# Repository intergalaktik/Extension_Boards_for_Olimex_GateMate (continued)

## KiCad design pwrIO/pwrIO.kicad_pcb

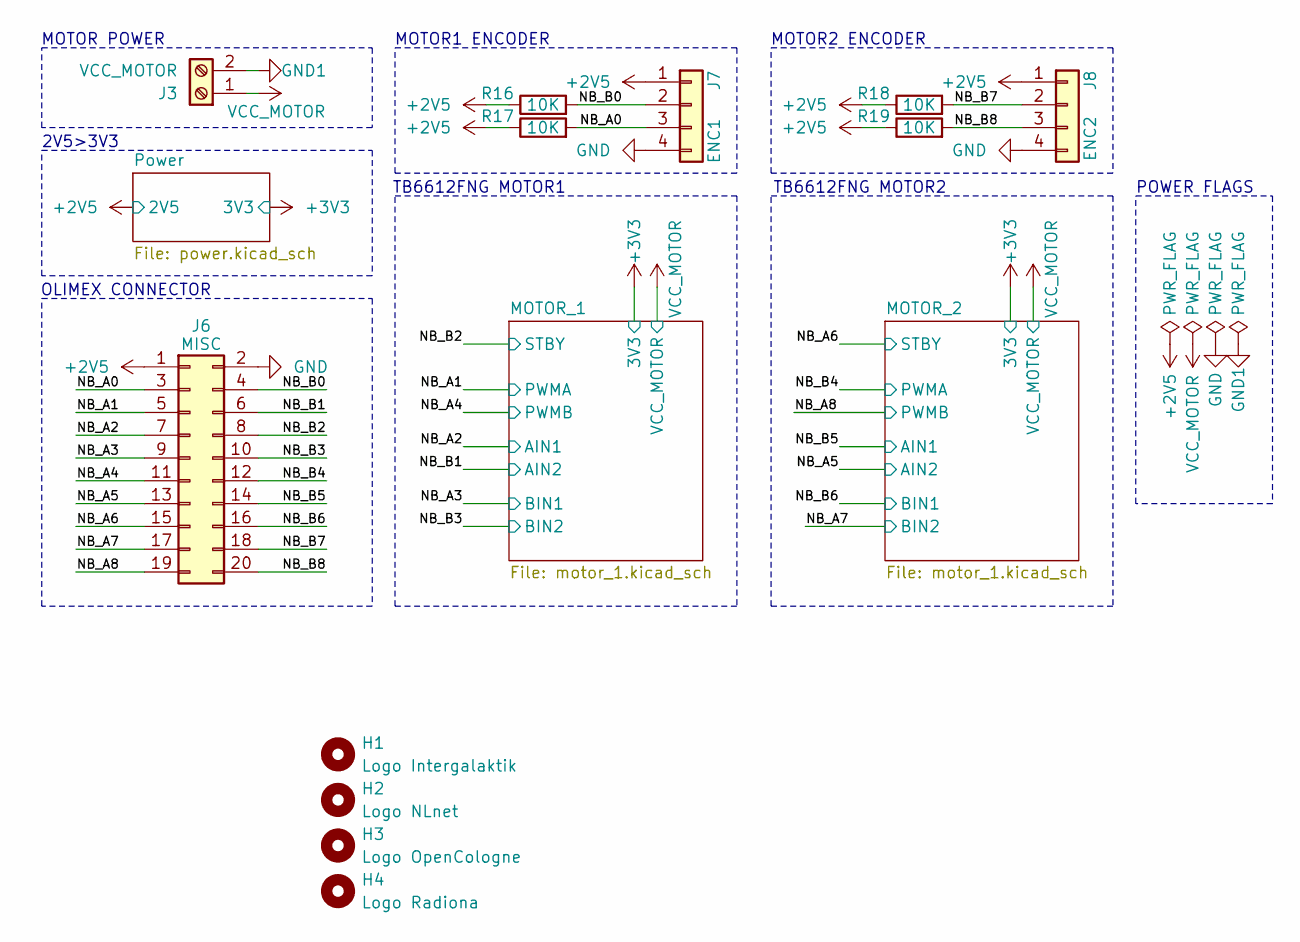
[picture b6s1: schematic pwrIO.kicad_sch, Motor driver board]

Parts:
H1: Logo Intergalaktik; intergalaktik
H2: Logo NLnet; nlnet
H3: Logo OpenCologne; open_cologne
H4: Logo Radiona; radiona
J3: VCC_MOTOR; TerminalBlock_Phoenix_MPT-0,5-2-2.54_1x02_P2.54mm_Horizontal
J6: MISC; PinSocket_2x10_P2.54mm_Vertical_SMD
J7: ENC1; PinSocket_1x04_P2.54mm_Vertical
J8: ENC2; PinSocket_1x04_P2.54mm_Vertical
R16, R17, R18, R19: 10K; R_0402_1005Metric

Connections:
+2V5: J6.1, J7.1, J8.1, R16.1, R17.1, R18.1, R19.1; also elsewhere on the board
/NB_A0: J6.3, J7.3, R17.2
/NB_A1: J6.5; also elsewhere on the board
/NB_A2: J6.7; also elsewhere on the board
/NB_A3: J6.9; also elsewhere on the board
/NB_A4: J6.11; also elsewhere on the board
/NB_A5: J6.13; also elsewhere on the board
/NB_A6: J6.15; also elsewhere on the board
/NB_A7: J6.17; also elsewhere on the board
/NB_A8: J6.19; also elsewhere on the board
/NB_B0: J6.4, J7.2, R16.2
/NB_B1: J6.6; also elsewhere on the board
/NB_B2: J6.8; also elsewhere on the board
/NB_B3: J6.10; also elsewhere on the board
/NB_B4: J6.12; also elsewhere on the board
/NB_B5: J6.14; also elsewhere on the board
/NB_B6: J6.16; also elsewhere on the board
/NB_B7: J6.18, J8.2, R18.2
/NB_B8: J6.20, J8.3, R19.2
GND: J6.2, J7.4, J8.4; also elsewhere on the board
GND1: J3.2; also elsewhere on the board
VCC_MOTOR: J3.1; also elsewhere on the board

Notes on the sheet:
OLIMEX CONNECTOR
TB6612FNG MOTOR1
MOTOR1 ENCODER
TB6612FNG MOTOR2
MOTOR2 ENCODER
2V5>3V3
POWER FLAGS
MOTOR POWER

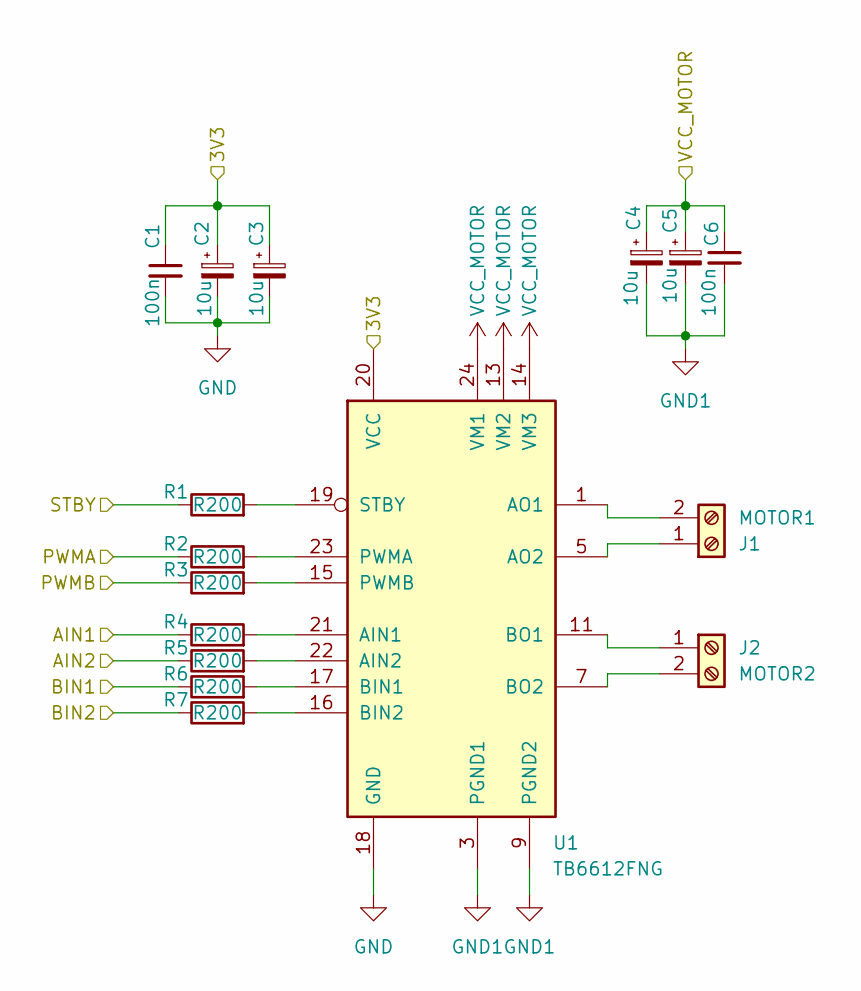
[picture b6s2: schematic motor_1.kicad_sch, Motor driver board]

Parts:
C1, C6: 100n; C_0402_1005Metric
C2, C3, C4, C5: 10u; CP_EIA-3216-18_Kemet-A
J1: MOTOR1; TerminalBlock_Phoenix_MPT-0,5-2-2.54_1x02_P2.54mm_Horizontal
J2: MOTOR2; TerminalBlock_Phoenix_MPT-0,5-2-2.54_1x02_P2.54mm_Horizontal
R1, R2, R3, R4, R5, R6, R7: R200; R_0402_1005Metric
U1: TB6612FNG; SSOP-24_5.3x8.2mm_P0.65mm

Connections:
+3V3: C1.1, C2.1, C3.1, U1.20 (VCC); also elsewhere on the board
/NB_A1: R2.1; also elsewhere on the board
/NB_A2: R4.1; also elsewhere on the board
/NB_A3: R6.1; also elsewhere on the board
/NB_A4: R3.1; also elsewhere on the board
/NB_B1: R5.1; also elsewhere on the board
/NB_B2: R1.1; also elsewhere on the board
/NB_B3: R7.1; also elsewhere on the board
GND: C1.2, C2.2, C3.2, U1.18 (GND); also elsewhere on the board
GND1: C4.2, C5.2, C6.2, U1.3 (PGND1), U1.4 (PGND1), U1.9 (PGND2), U1.10 (PGND2); also elsewhere on the board
unnamed: J1.1, U1.5 (AO2), U1.6 (AO2)
unnamed: J1.2, U1.1 (AO1), U1.2 (AO1)
unnamed: J2.1, U1.11 (BO1), U1.12 (BO1)
unnamed: J2.2, U1.7 (BO2), U1.8 (BO2)
unnamed: R4.2, U1.21 (AIN1)
unnamed: R5.2, U1.22 (AIN2)
unnamed: R6.2, U1.17 (BIN1)
unnamed: R7.2, U1.16 (BIN2)
unnamed: R2.2, U1.23 (PWMA)
unnamed: R3.2, U1.15 (PWMB)
unnamed: R1.2, U1.19 (STBY)
VCC_MOTOR: C4.1, C5.1, C6.1, U1.13 (VM2), U1.14 (VM3), U1.24 (VM1); also elsewhere on the board

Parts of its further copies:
C7, C12: 100n; C_0402_1005Metric
C8, C9, C10, C11: 10u; CP_EIA-3216-18_Kemet-A
J4: MOTOR1; TerminalBlock_Phoenix_MPT-0,5-2-2.54_1x02_P2.54mm_Horizontal
J5: MOTOR2; TerminalBlock_Phoenix_MPT-0,5-2-2.54_1x02_P2.54mm_Horizontal
R8, R9, R10, R11, R12, R13, R14: R200; R_0402_1005Metric
U2: TB6612FNG; SSOP-24_5.3x8.2mm_P0.65mm

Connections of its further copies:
+3V3: C7.1, C8.1, C9.1, U2.20 (VCC); also elsewhere on the board
/NB_A5: R12.1; also elsewhere on the board
/NB_A6: R8.1; also elsewhere on the board
/NB_A7: R14.1; also elsewhere on the board
/NB_A8: R10.1; also elsewhere on the board
/NB_B4: R9.1; also elsewhere on the board
/NB_B5: R11.1; also elsewhere on the board
/NB_B6: R13.1; also elsewhere on the board
GND: C7.2, C8.2, C9.2, U2.18 (GND); also elsewhere on the board
GND1: C10.2, C11.2, C12.2, U2.3 (PGND1), U2.4 (PGND1), U2.9 (PGND2), U2.10 (PGND2); also elsewhere on the board
unnamed: J4.1, U2.5 (AO2), U2.6 (AO2)
unnamed: J4.2, U2.1 (AO1), U2.2 (AO1)
unnamed: J5.1, U2.11 (BO1), U2.12 (BO1)
unnamed: J5.2, U2.7 (BO2), U2.8 (BO2)
unnamed: R11.2, U2.21 (AIN1)
unnamed: R12.2, U2.22 (AIN2)
unnamed: R13.2, U2.17 (BIN1)
unnamed: R14.2, U2.16 (BIN2)
unnamed: R9.2, U2.23 (PWMA)
unnamed: R10.2, U2.15 (PWMB)
unnamed: R8.2, U2.19 (STBY)
VCC_MOTOR: C10.1, C11.1, C12.1, U2.13 (VM2), U2.14 (VM3), U2.24 (VM1); also elsewhere on the board

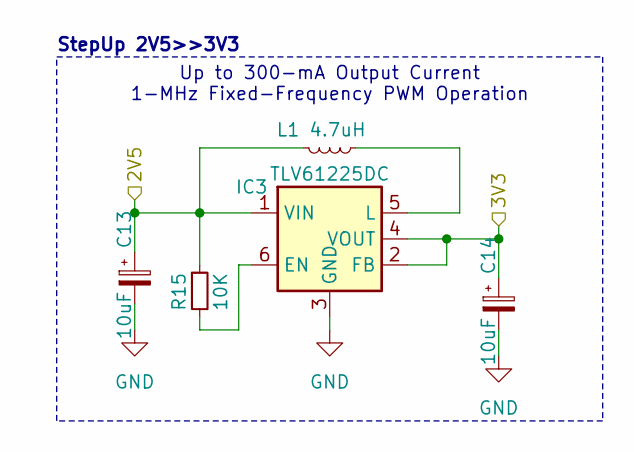
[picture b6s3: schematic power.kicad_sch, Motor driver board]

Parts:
C13, C14: 10uF; C_0603_1608Metric
IC3: TLV61225DC; SOT-363_SC-70-6
L1: 4.7uH; L_0603_1608Metric
R15: 10K; R_0402_1005Metric; MPN RC0603FR-071K1L; Mouser 603-RC0603FR-071K1L

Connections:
+2V5: C13.1, IC3.1 (VIN), L1.2, R15.1; also elsewhere on the board
+3V3: C14.1, IC3.2 (FB), IC3.4 (VOUT); also elsewhere on the board
GND: C13.2, C14.2, IC3.3 (GND); also elsewhere on the board

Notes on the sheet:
Up to 300-mA Output Current 1-MHz Fixed-Frequency PWM Operation
StepUp 2V5>>3V3

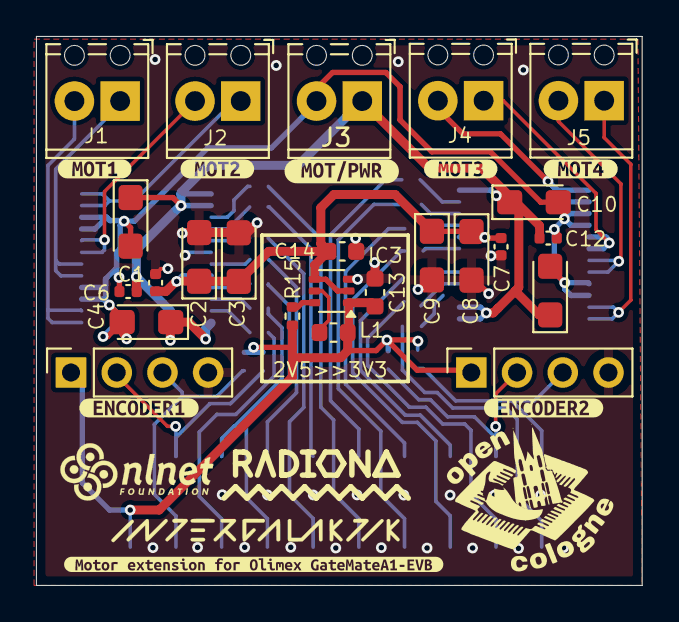
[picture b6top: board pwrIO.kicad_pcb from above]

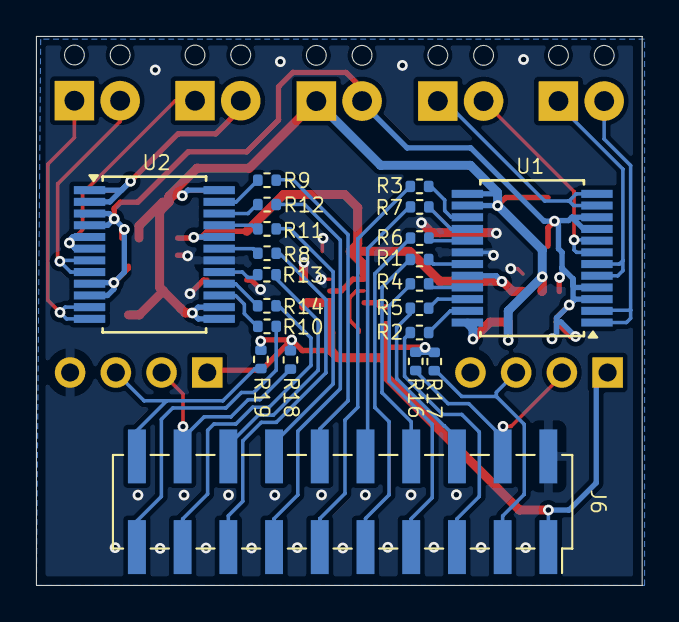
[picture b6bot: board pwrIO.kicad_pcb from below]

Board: 4 copper layers, 33.7 x 30.5 mm, 57 parts (21 on the bottom side), 45 nets.

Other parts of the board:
kibuzzard-674632A1: G***; kibuzzard-674632A1
kibuzzard-674632D6: G***; kibuzzard-674632D6
kibuzzard-674632E9: G***; kibuzzard-674632E9
kibuzzard-674632F5: G***; kibuzzard-674632F5
kibuzzard-6746333A: G***; kibuzzard-6746333A
kibuzzard-6746334D: G***; kibuzzard-6746334D
kibuzzard-67463311: G***; kibuzzard-67463311
kibuzzard-67464255: G***; kibuzzard-67464255

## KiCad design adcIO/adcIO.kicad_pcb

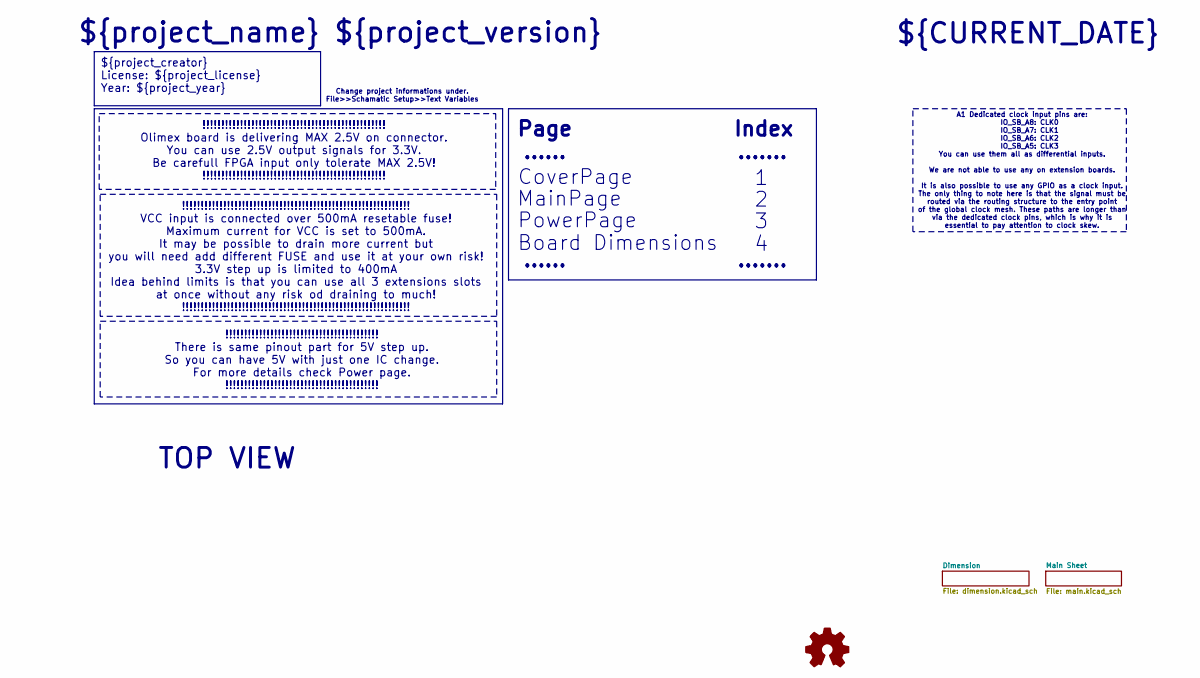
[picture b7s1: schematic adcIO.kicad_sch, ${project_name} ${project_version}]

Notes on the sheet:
${project_creator} License: ${project_license} Year: ${project_year}
Index
!!!!!!!!!!!!!!!!!!!!!!!!!!!!!!!!!!!!!!!!!!!!!!!!!!!!!!!!!!!!! VCC input is connected over 500mA resetable fuse! Maximum current for VCC is set to 500mA. It may be possible to drain more current but you will need add different FUSE and use it at your own risk! 3.3V step up is limited to 400mA Idea b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
!!!!!!!!!!!!!!!!!!!!!!!!!!!!!!!!!!!!!!!!!!!!!!!!! Olimex board is delivering MAX 2.5V on connector. You can use 2.5V output signals for 3.3V. Be carefull FPGA input only tolerate MAX 2.5V! !!!!!!!!!!!!!!!!!!!!!!!!!!!!!!!!!!!!!!!!!!!!!!!!!
!!!!!!!!!!!!!!!!!!!!!!!!!!!!!!!!!!!!!!!!! There is same pinout part for 5V step up. So you can have 5V with just one IC change. For more details check Power page. !!!!!!!!!!!!!!!!!!!!!!!!!!!!!!!!!!!!!!!!!
......
PowerPage
Change project informations under. File>>Schamatic Setup>>Text Variables
.......
A1 Dedicated clock input pins are: IO_SB_A8: CLK0 IO_SB_A7: CLK1 IO_SB_A6: CLK2 IO_SB_A5: CLK3 You can use them all as differential inputs. We are not able to use any on extension boards. It is also possible to use any GPIO as a clock input. The only thing to note here is that the signal must be ro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
CoverPage
Board Dimensions
MainPage
${CURRENT_DATE}
${project_name} ${project_version}
TOP VIEW
Page

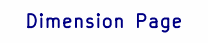
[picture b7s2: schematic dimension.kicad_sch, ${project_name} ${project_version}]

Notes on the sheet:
Dimension Page

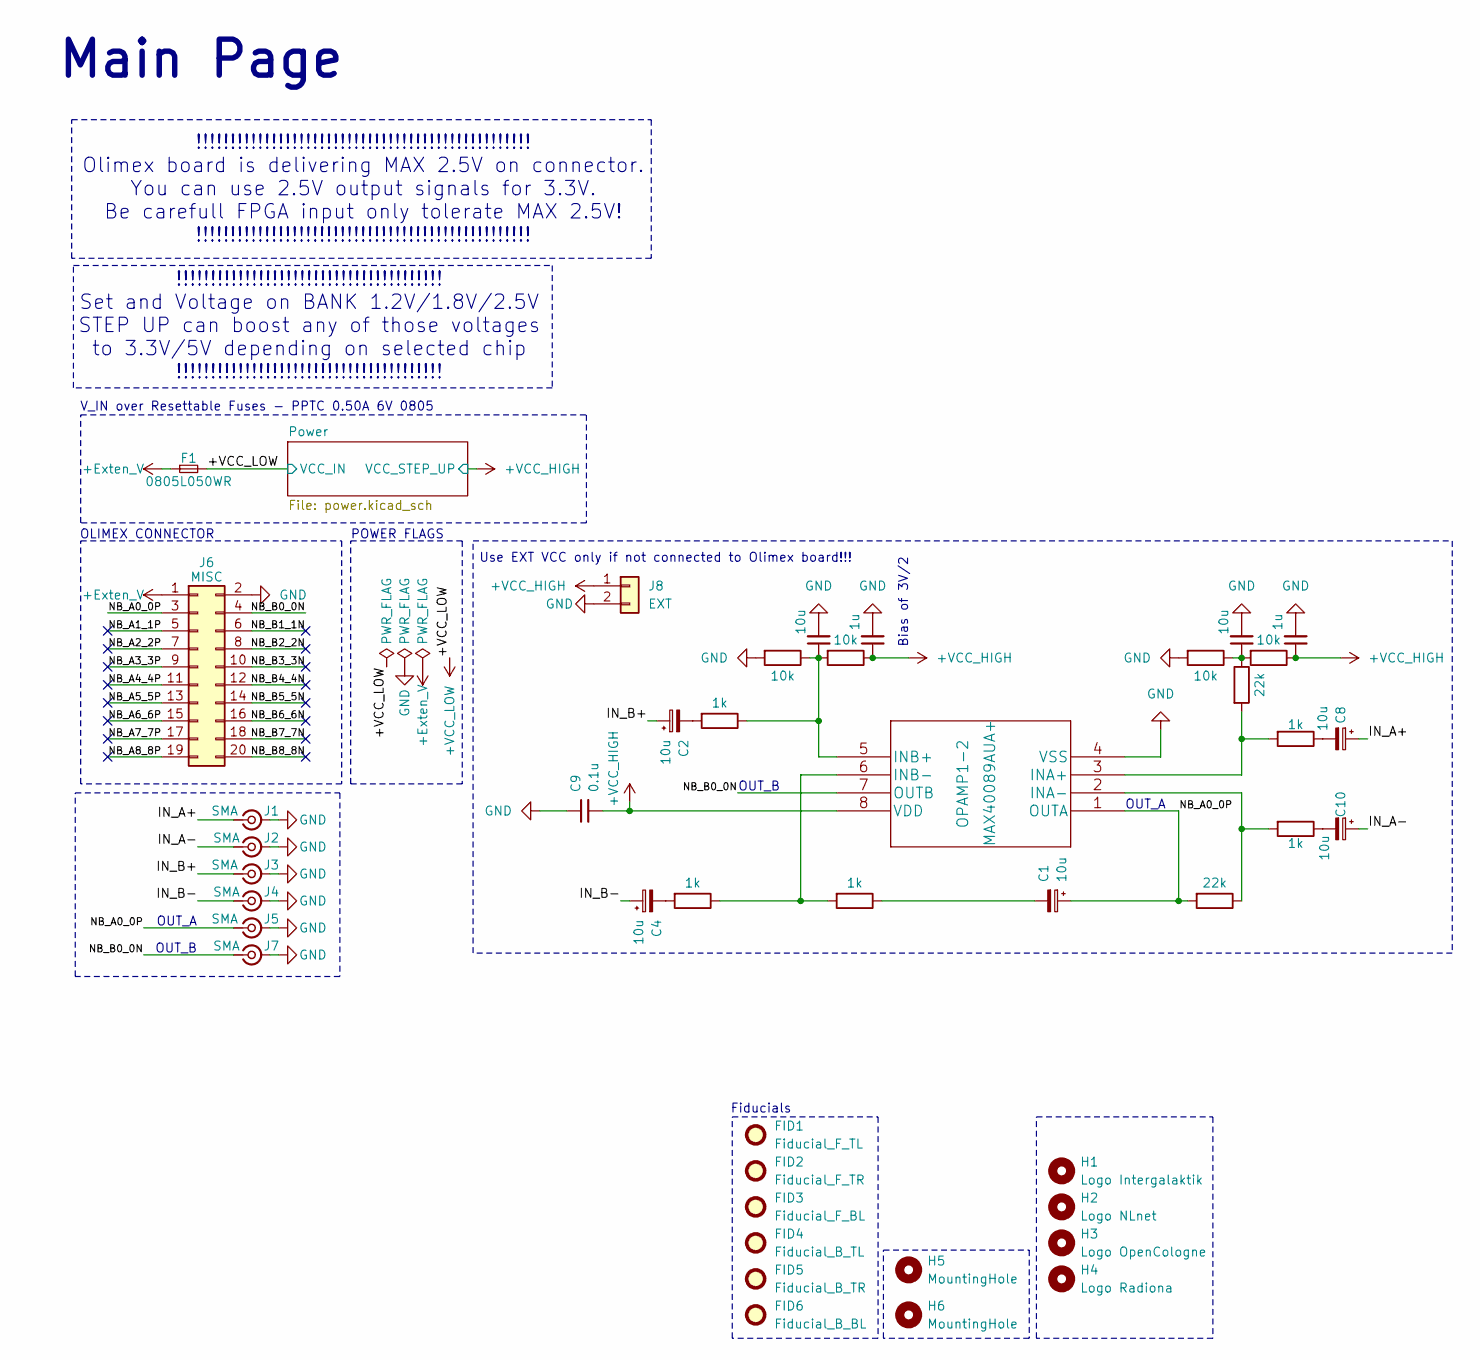
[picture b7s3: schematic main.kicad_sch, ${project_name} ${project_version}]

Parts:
C1, C2, C4, C8, C10: 10u; CP_EIA-1608-10_AVX-L
C3, C6: 10u; C_0603_1608Metric
C5, C7: 1u; C_0603_1608Metric
C9: 0.1u; C_0402_1005Metric
F1: 0805L050WR; Fuse_0805_2012Metric
FID1: Fiducial_F_TL; Fiducial_0.5mm_Mask1mm
FID2: Fiducial_F_TR; Fiducial_0.5mm_Mask1mm
FID3: Fiducial_F_BL; Fiducial_0.5mm_Mask1mm
FID4: Fiducial_B_TL; Fiducial_0.5mm_Mask1mm
FID5: Fiducial_B_TR; Fiducial_0.5mm_Mask1mm
FID6: Fiducial_B_BL; Fiducial_0.5mm_Mask1mm
H1: Logo Intergalaktik; intergalaktik
H2: Logo NLnet; nlnet
H3: Logo OpenCologne; open_cologne_small
H4: Logo Radiona; radiona_small
H5, H6: MountingHole; MountingHole_2.2mm_M2
J1, J2, J3, J4, J5, J7: SMA; SMA_Amphenol_901-144_Vertical
J6: MISC; PinSocket_2x10_P2.54mm_Vertical_SMD
J8: EXT; PinHeader_1x02_P2.54mm_Vertical
OPAMP1-2: MAX40089AUA+; SOP65P490X110-8N
R1, R2, R8, R9, R10: 1k; R_0402_1005Metric
R3, R4, R5, R6: 10k; R_0402_1005Metric
R7, R11: 22k; R_0402_1005Metric

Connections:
+Exten_V: F1.1, J6.1
+VCC_HIGH: C5.1, C7.1, C9.2, J8.1, OPAMP1-2.8 (VDD), R4.1, R6.1; also elsewhere on the board
+VCC_LOW: F1.2; also elsewhere on the board
/Main Sheet/IN_A+: C8.1, J1.1 (In)
/Main Sheet/IN_A-: C10.1, J2.1 (In)
/Main Sheet/IN_B+: C2.1, J3.1 (In)
/Main Sheet/IN_B-: C4.1, J4.1 (In)
/Main Sheet/NB_A0_0P: C1.1, J5.1 (In), J6.3, OPAMP1-2.1 (OUTA), R11.2
/Main Sheet/NB_A1_1P: J6.5
/Main Sheet/NB_A2_2P: J6.7
/Main Sheet/NB_A3_3P: J6.9
/Main Sheet/NB_A4_4P: J6.11
/Main Sheet/NB_A5_5P: J6.13
/Main Sheet/NB_A6_6P: J6.15
/Main Sheet/NB_A7_7P: J6.17
/Main Sheet/NB_A8_8P: J6.19
/Main Sheet/NB_B0_0N: J6.4, J7.1 (In), OPAMP1-2.7 (OUTB)
/Main Sheet/NB_B1_1N: J6.6
/Main Sheet/NB_B2_2N: J6.8
/Main Sheet/NB_B3_3N: J6.10
/Main Sheet/NB_B4_4N: J6.12
/Main Sheet/NB_B5_5N: J6.14
/Main Sheet/NB_B6_6N: J6.16
/Main Sheet/NB_B7_7N: J6.18
/Main Sheet/NB_B8_8N: J6.20
GND: C3.2, C5.2, C6.2, C7.2, C9.1, J1.2 (Ext), J2.2 (Ext), J3.2 (Ext), J4.2 (Ext), J5.2 (Ext), J6.2, J7.2 (Ext), J8.2, OPAMP1-2.4 (VSS), R3.2, R5.2; also elsewhere on the board
unnamed: C1.2, R10.1
unnamed: C2.2, R1.2
unnamed: C4.2, R2.2
unnamed: C6.1, R5.1, R6.2, R7.1
unnamed: C8.2, R8.1
unnamed: C10.2, R9.1
unnamed: OPAMP1-2.3 (INA+), R7.2, R8.2
unnamed: OPAMP1-2.2 (INA-), R9.2, R11.1
unnamed: C3.1, OPAMP1-2.5 (INB+), R1.1, R3.1, R4.2
unnamed: OPAMP1-2.6 (INB-), R2.1, R10.2

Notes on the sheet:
OUT_A
POWER FLAGS
V_IN over Resettable Fuses - PPTC 0.50A 6V 0805
OUT_B
!!!!!!!!!!!!!!!!!!!!!!!!!!!!!!!!!!!!!!!!!!!!!!!!! Olimex board is delivering MAX 2.5V on connector. You can use 2.5V output signals for 3.3V. Be carefull FPGA input only tolerate MAX 2.5V! !!!!!!!!!!!!!!!!!!!!!!!!!!!!!!!!!!!!!!!!!!!!!!!!!
Fiducials
Use EXT VCC only if not connected to Olimex board!!!
OLIMEX CONNECTOR
Bias of 3V/2
Main Page
!!!!!!!!!!!!!!!!!!!!!!!!!!!!!!!!!!!!!!! Set and Voltage on BANK 1.2V/1.8V/2.5V STEP UP can boost any of those voltages to 3.3V/5V depending on selected chip !!!!!!!!!!!!!!!!!!!!!!!!!!!!!!!!!!!!!!!

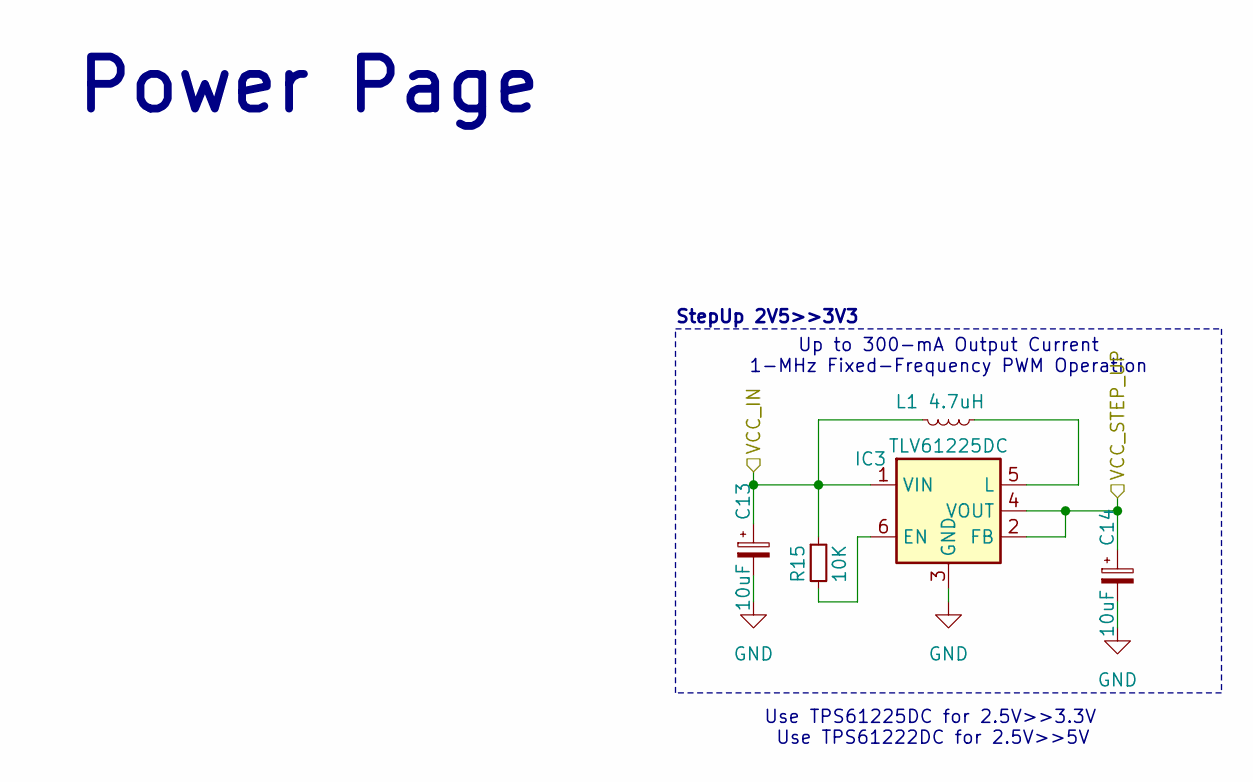
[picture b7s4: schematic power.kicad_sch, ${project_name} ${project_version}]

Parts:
C13, C14: 10uF; C_0603_1608Metric
IC3: TLV61225DC; SOT-363_SC-70-6
L1: 4.7uH; L_0603_1608Metric
R15: 10K; R_0402_1005Metric; MPN RC0603FR-071K1L; Mouser 603-RC0603FR-071K1L

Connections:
+VCC_HIGH: C14.1, IC3.2 (FB), IC3.4 (VOUT); also elsewhere on the board
+VCC_LOW: C13.1, IC3.1 (VIN), L1.2, R15.1; also elsewhere on the board
GND: C13.2, C14.2, IC3.3 (GND); also elsewhere on the board
unnamed: IC3.6 (EN), R15.2
unnamed: IC3.5 (L), L1.1

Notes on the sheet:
Up to 300-mA Output Current 1-MHz Fixed-Frequency PWM Operation
Use TPS61222DC for 2.5V>>5V
Power Page
StepUp 2V5>>3V3
Use TPS61225DC for 2.5V>>3.3V

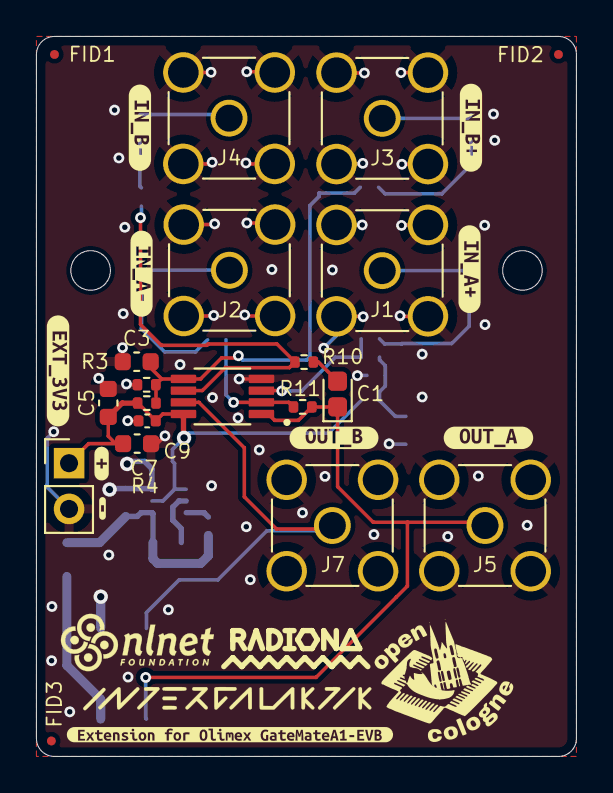
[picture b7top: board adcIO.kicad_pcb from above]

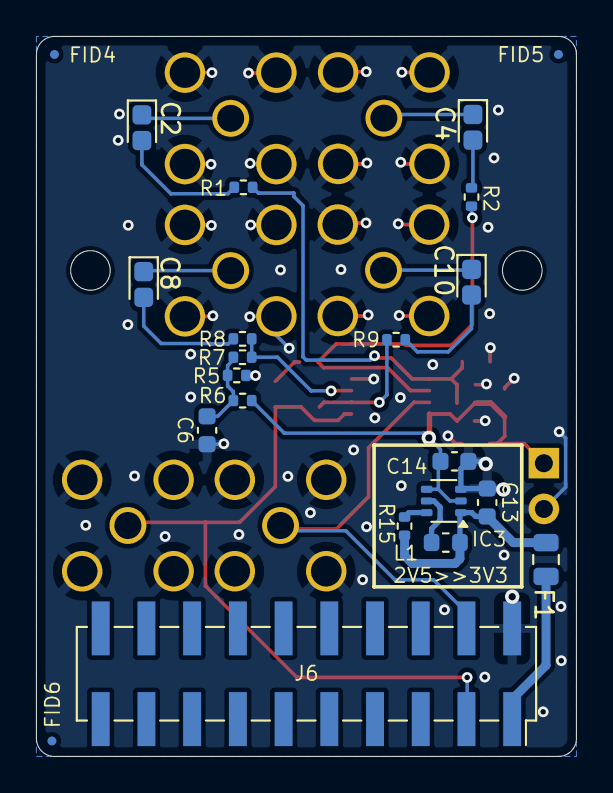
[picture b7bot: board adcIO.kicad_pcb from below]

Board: 4 copper layers, 30.0 x 40.0 mm, 58 parts (22 on the bottom side), 22 nets.

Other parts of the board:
kibuzzard-674D68C8: G***; kibuzzard-674D68C8
kibuzzard-67560CBC: G***; kibuzzard-67560CBC
kibuzzard-67560CDF: G***; kibuzzard-67560CDF
kibuzzard-67560D10: G***; kibuzzard-67560D10
kibuzzard-67560D36: G***; kibuzzard-67560D36
kibuzzard-67560E96: G***; kibuzzard-67560E96
kibuzzard-67560ECB: G***; kibuzzard-67560ECB
kibuzzard-67561DC2: G***; kibuzzard-67561DC2
kibuzzard-67561FBD: G***; kibuzzard-67561FBD
kibuzzard-6756200A: G***; kibuzzard-6756200A

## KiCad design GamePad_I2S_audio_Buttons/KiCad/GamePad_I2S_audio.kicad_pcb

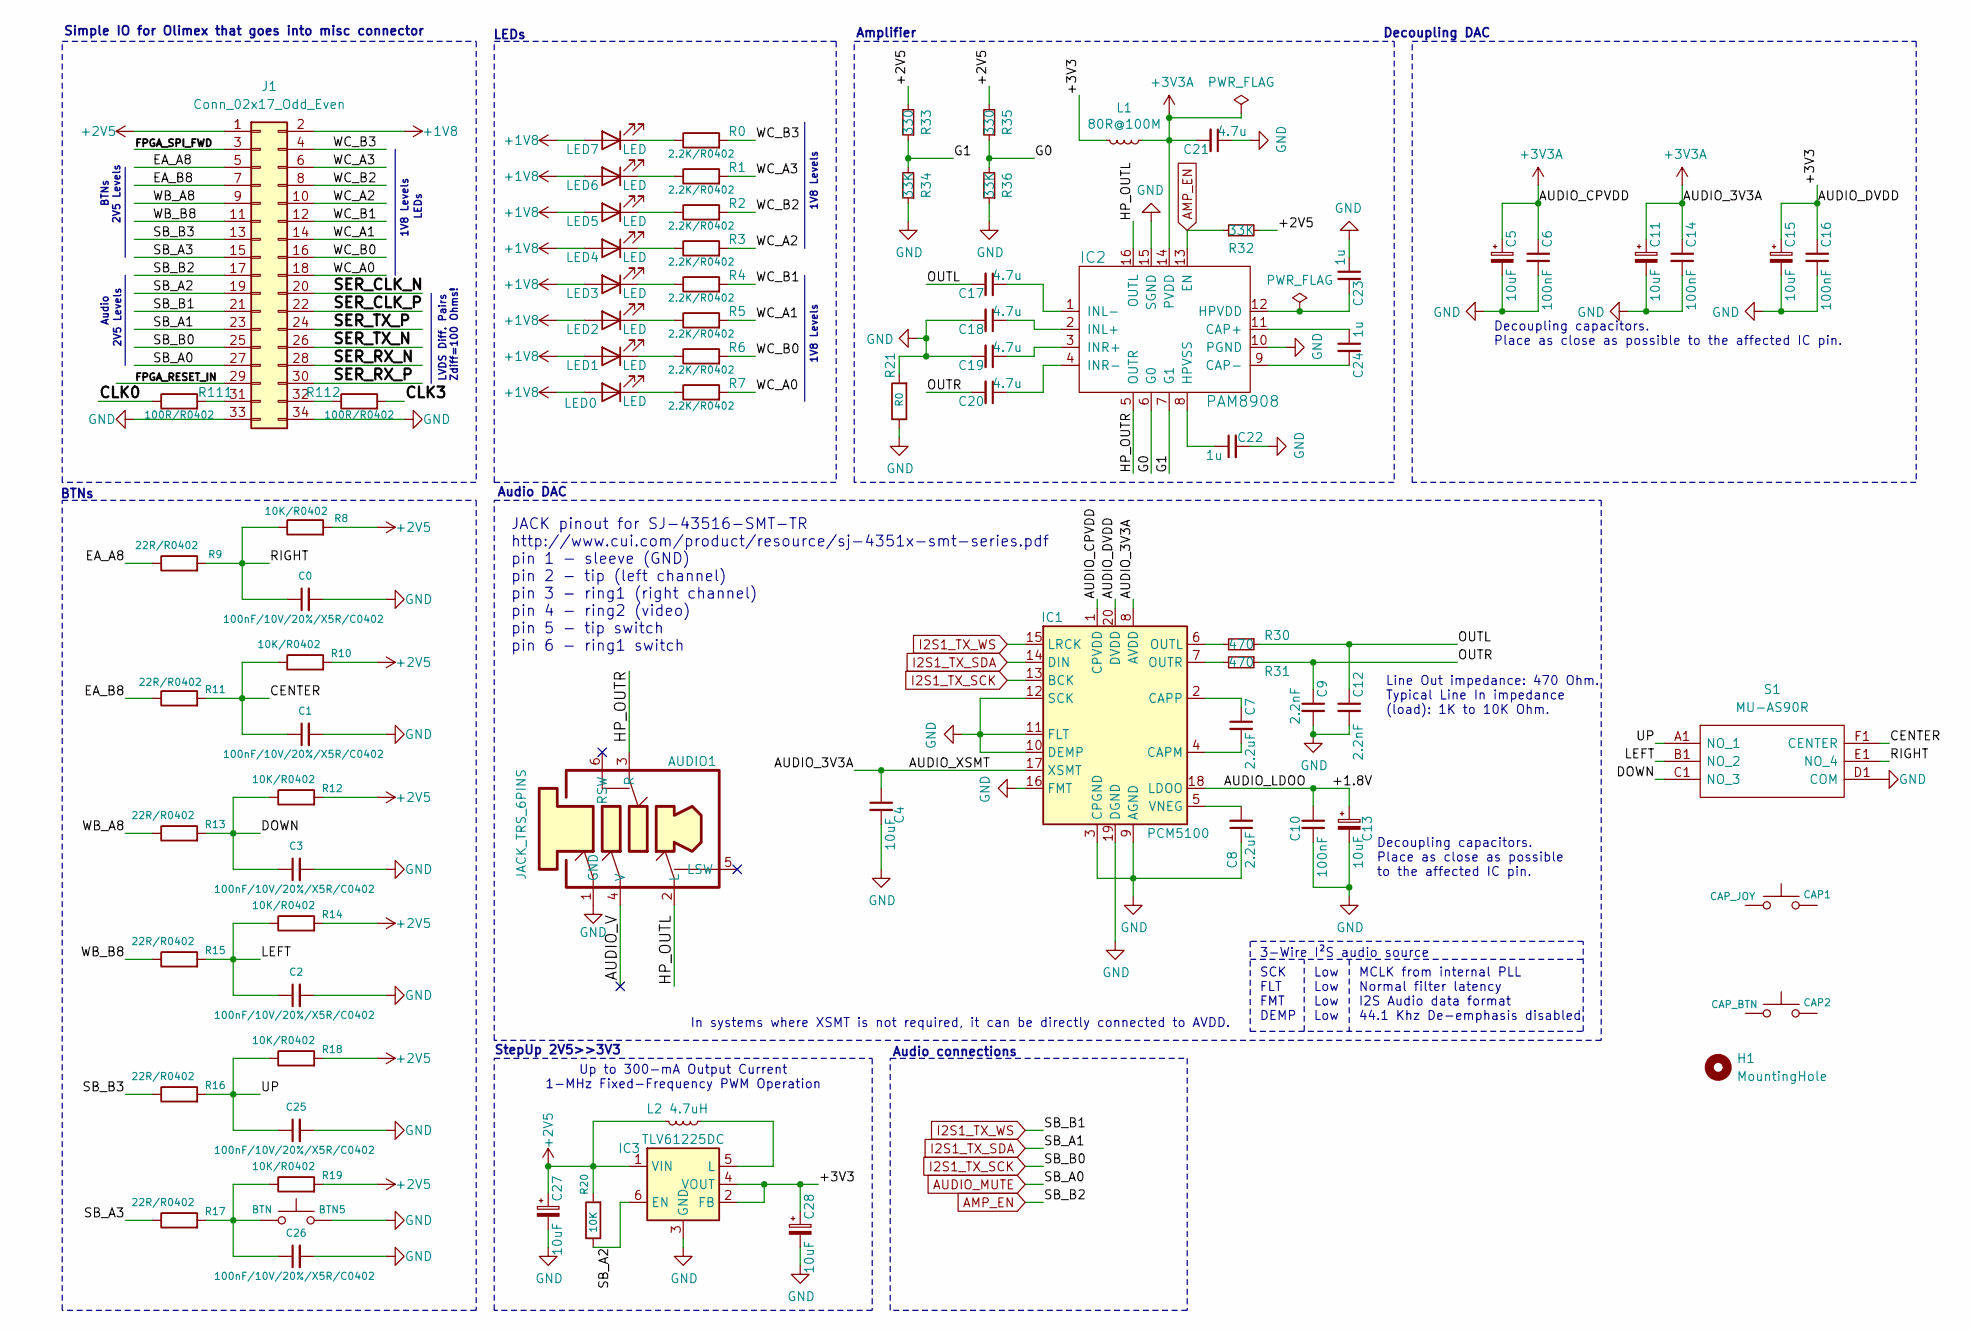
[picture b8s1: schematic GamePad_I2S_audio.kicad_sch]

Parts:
AUDIO1: JACK_TRS_6PINS; CUI_SJ-43516-SMT; MPN SJ-43516-SMT-TR; Mouser 490-SJ43515TS-SMT-TR
BTN5: BTN; B3FS4055P
C0, C1, C2, C3, C25, C26: 100nF/10V/20%/X5R/C0402; C_0402_1005Metric
C4, C5, C11, C13, C15, C27, C28: 10uF; C_0603_1608Metric
C6, C10, C14, C16: 100nF; C_0402_1005Metric
C7, C8: 2.2uF; C_0402_1005Metric
C9, C12: 2.2nF; C_0402_1005Metric
C17, C18, C19, C20, C21: 4.7u; C_0603_1608Metric
C22, C23, C24: 1u; C_0603_1608Metric
CAP1: CAP_JOY; TestPoint_Pad_1.0x1.0mm
CAP2: CAP_BTN; TestPoint_Pad_1.0x1.0mm
H1: MountingHole; MountingHole_2mm
IC1: PCM5100; TSSOP-20_4.4x6.5mm_P0.65mm
IC2: PAM8908; QFN-16-1EP_3x3mm_P0.5mm_EP1.7x1.7mm_ThermalVias
IC3: TLV61225DC; SOT-363_SC-70-6
J1: Conn_02x17_Odd_Even; PinSocket_2x17_P2.54mm_Vertical_SMD
L1: 80R@100M; L_0603_1608Metric
L2: 4.7uH; L_0603_1608Metric
LED0, LED1, LED2, LED3, LED4, LED5, LED6, LED7: LED; LED_0603_1608Metric
R0, R1, R2, R3, R4, R5, R6, R7: 2.2K/R0402; R_0402_1005Metric
R8, R10, R12, R14, R18, R19: 10K/R0402; R_0402_1005Metric
R9, R11, R13, R15, R16, R17: 22R/R0402; R_0402_1005Metric
R20: 10K; R_0402_1005Metric
R21: R0; R_0402_1005Metric
R30, R31: 470; R_0402_1005Metric
R32, R34, R36: 33K; R_0402_1005Metric
R33, R35: 330; R_0402_1005Metric
R111, R112: 100R/R0402; R_0402_1005Metric
S1: MU-AS90R; MUAS90R; Mouser Part Number 642-MU-AS90R

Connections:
+1V8: J1.2, LED0.2 (A), LED1.2 (A), LED2.2 (A), LED3.2 (A), LED4.2 (A), LED5.2 (A), LED6.2 (A), LED7.2 (A)
+2V5: C27.1, IC3.1 (VIN), J1.1, L2.2, R8.2, R10.2, R12.2, R14.2, R18.2, R19.2, R20.2, R32.2, R33.2, R35.2
+3V3A: C4.1, C5.1, C6.1, C11.1, C14.1, C21.2, IC1.1 (CPVDD), IC1.8 (AVDD), IC1.17 (XSMT), IC2.14 (PVDD), L1.1
/+1.8V: C10.1, C13.1, IC1.18 (LDOO)
/+3V3: C15.1, C16.1, C28.1, IC1.20 (DVDD), IC3.2 (FB), IC3.4 (VOUT), L1.2
/AUDIO_V: AUDIO1.4 (V)
/CENTER: C1.1, R10.1, R11.2, S1.F1 (CENTER)
/CLK0: R111.1
/CLK3: R112.2
/DOWN: C3.1, R12.1, R13.2, S1.C1 (NO_3)
/EA_A8: J1.5, R9.1
/EA_B8: J1.7, R11.1
/FPGA_RESET_IN: J1.29
/FPGA_SPI_FWD: J1.3
/G0: IC2.6 (G0), R35.1, R36.2
/G1: IC2.7 (G1), R33.1, R34.2
/HP_OUTL: AUDIO1.2 (L), IC2.16 (OUTL)
/HP_OUTR: AUDIO1.3 (R), IC2.5 (OUTR)
/LEFT: C2.1, R14.1, R15.2, S1.B1 (NO_2)
/OUTL: C12.1, C17.2, R30.1
/OUTR: C9.1, C20.2, R31.1
/RIGHT: C0.1, R8.1, R9.2, S1.E1 (NO_4)
/SB_A2: IC3.6 (EN), J1.19, R20.1
/SB_A3: J1.15, R17.1
/SB_B3: J1.13, R16.1
/SER_CLK_N: J1.20
/SER_CLK_P: J1.22
/SER_RX_N: J1.28
/SER_RX_P: J1.30
/SER_TX_N: J1.26
/SER_TX_P: J1.24
/UP: C25.1, R16.2, R18.1, S1.A1 (NO_1)
/WB_A8: J1.9, R13.1
/WB_B8: J1.11, R15.1
/WC_A0: J1.18, R7.2
/WC_A1: J1.14, R5.2
/WC_A2: J1.10, R3.2
/WC_A3: J1.6, R1.2
/WC_B0: J1.16, R6.2
/WC_B1: J1.12, R4.2
/WC_B2: J1.8, R2.2
/WC_B3: J1.4, R0.2
AMP_EN: IC2.13 (EN), J1.17, R32.1
AUDIO_MUTE: J1.27
GND: AUDIO1.1 (GND), BTN5.2, C0.2, C1.2, C2.2, C3.2, C4.2, C5.2, C6.2, C8.1, C9.2, C10.2, C11.2, C12.2, C13.2, C14.2, C15.2, C16.2, C18.2, C19.2, C21.1, C22.2, C23.1, C25.2, C26.2, C27.2, C28.2, IC1.3 (CPGND), IC1.9 (AGND), IC1.10 (DEMP), IC1.11 (FLT), IC1.12 (SCK), IC1.16 (FMT), IC1.19 (DGND), IC2.10 (PGND), IC2.15 (SGND), IC3.3 (GND), J1.33, J1.34, R21.1, R21.2, R34.1, R36.1, S1.D1 (COM)
I2S1_TX_SCK: IC1.13 (BCK), J1.25
I2S1_TX_SDA: IC1.14 (DIN), J1.23
I2S1_TX_WS: IC1.15 (LRCK), J1.21
unnamed: BTN5.3 (1), C26.1, R17.2, R19.1
unnamed: C7.2, IC1.4 (CAPM)
unnamed: C7.1, IC1.2 (CAPP)
unnamed: IC1.6 (OUTL), R30.2
unnamed: IC1.7 (OUTR), R31.2
unnamed: C8.2, IC1.5 (VNEG)
unnamed: C24.1, IC2.11 (CAP+)
unnamed: C24.2, IC2.9 (CAP-)
unnamed: C23.2, IC2.12 (HPVDD)
unnamed: C22.1, IC2.8 (HPVSS)
unnamed: C18.1, IC2.2 (INL+)
unnamed: C17.1, IC2.1 (INL-)
unnamed: C19.1, IC2.3 (INR+)
unnamed: C20.1, IC2.4 (INR-)
unnamed: IC3.5 (L), L2.1
unnamed: J1.31, R111.2
unnamed: J1.32, R112.1
unnamed: LED0.1 (K), R7.1
unnamed: LED1.1 (K), R6.1
unnamed: LED2.1 (K), R5.1
unnamed: LED3.1 (K), R4.1
unnamed: LED4.1 (K), R3.1
unnamed: LED5.1 (K), R2.1
unnamed: LED6.1 (K), R1.1
unnamed: LED7.1 (K), R0.1

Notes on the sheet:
2V5 Levels
1V8 Levels
Up to 300-mA Output Current 1-MHz Fixed-Frequency PWM Operation
Audio connections
Audio DAC
Line Out impedance: 470 Ohm. Typical Line In impedance (load): 1K to 10K Ohm.
StepUp 2V5>>3V3
BTNs
In systems where XSMT is not required, it can be directly connected to AVDD.
3-Wire I²S audio source
Low Low Low Low
Decoupling capacitors. Place as close as possible to the affected IC pin.
Amplifier
JACK pinout for SJ-43516-SMT-TR http://www.cui.com/product/resource/sj-4351x-smt-series.pdf pin 1 - sleeve (GND) pin 2 - tip (left channel) pin 3 - ring1 (right channel) pin 4 - ring2 (video) pin 5 - tip switch pin 6 - ring1 switch
LVDS Diff. Pairs Zdiff=100 Ohms!
SCK FLT FMT DEMP
MCLK from internal PLL Normal filter latency I2S Audio data format 44.1 Khz De-emphasis disabled
Audio
LEDs
Simple IO for Olimex that goes into misc connector
Decoupling capacitors. Place as close as possible to the affected IC pin.
Decoupling DAC

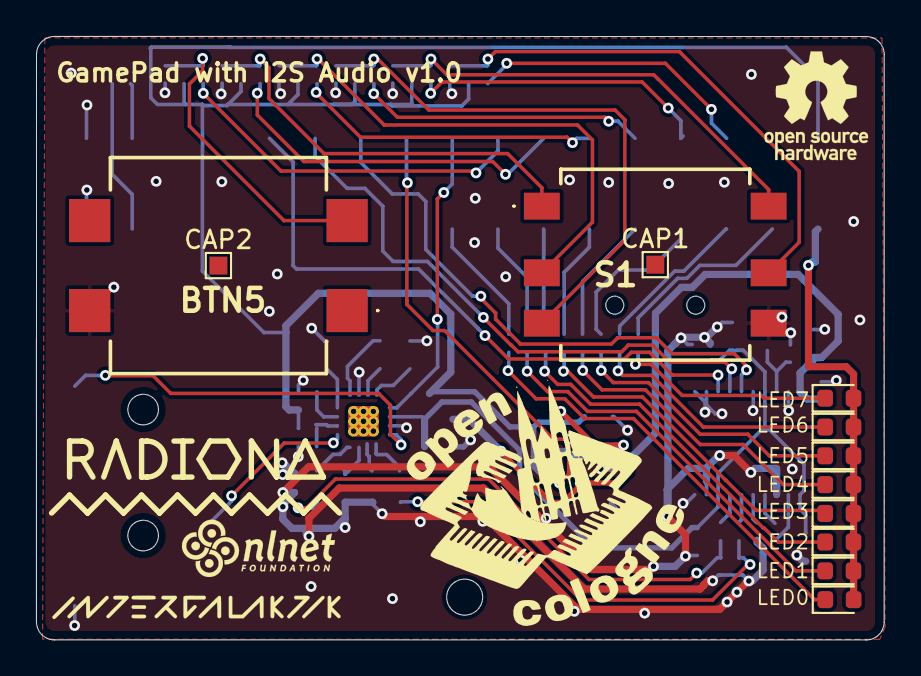
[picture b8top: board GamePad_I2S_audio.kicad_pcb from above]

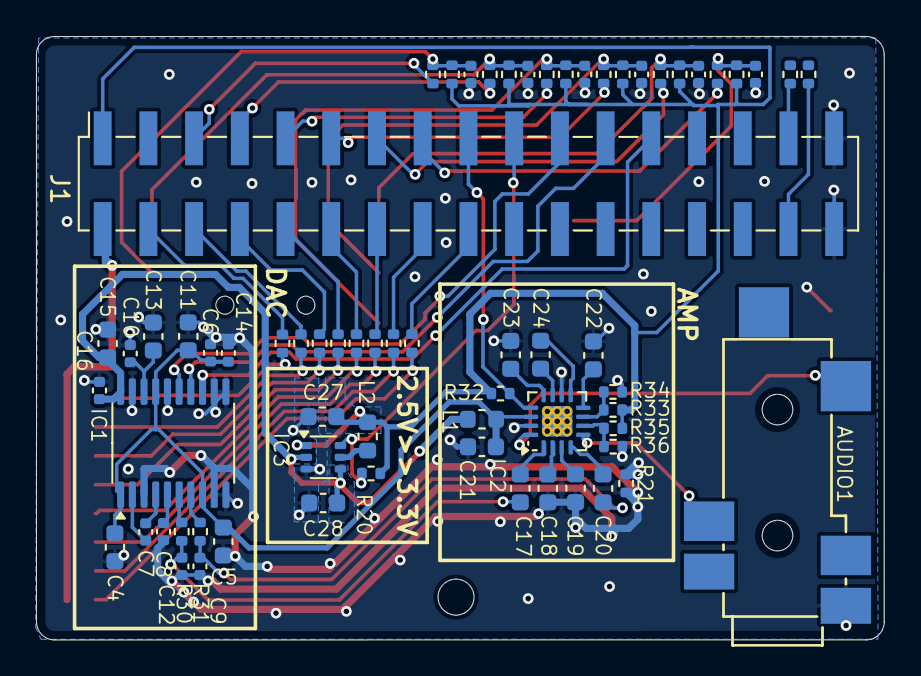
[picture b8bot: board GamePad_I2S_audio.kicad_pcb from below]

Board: 4 copper layers, 47.1 x 33.5 mm, 81 parts (67 on the bottom side), 61 nets.

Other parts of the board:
radiona: radiona

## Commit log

2024-10-16 initial version
2024-10-16 Cleanup - switch to 4layer
2024-10-16 Changing audio connector
2024-10-16 Adding picture
2024-10-16 Starting to work on version with more buttons and I2S audio
2024-10-16 Adding StepUP
2024-10-16 Adding initial schematics
2024-10-16 initial PCB setup
2024-10-16 Removing not needed file
2024-10-16 Adding schematic link
2024-10-18 Routing
2024-10-18 Adding new libs
2024-10-18 Better GND
2024-10-18 update schematics
2024-10-18 Update doc
2024-10-18 Sqitching to only one GND
2024-10-18 V1.0
2024-11-27 Adding initial USB and motor extension
2024-11-27 Check
2024-11-28 sch pcb
2024-11-28 Connecting encoder to 2.5V
2024-11-28 initial connection done
2024-11-28 Updating pdf - adding blender export
2024-11-29 Adding initial not routed dualTransition PCB
2024-11-29 Adding PULL UPs on LOW Level
2024-11-29 Adding PULL UPs on HIGH Level
2024-11-29 Adding diode footprint
2024-11-29 Adding initial timmer board
2024-11-29 Routing dualTranslarion
2024-11-29 Exporting dualTranslation schematic to pdf
2024-12-02 Adding initial extension template
2024-12-02 Extension template update
2024-12-02 Adding smaller logo footprints
2024-12-02 PCB update
2024-12-02 Adding license files
2024-12-02 Adding License
2024-12-02 Template update
2024-12-02 Adding license - update tmrIO
2024-12-02 dualTranslation update
2024-12-03 Adding git ignore
2024-12-03 Adding new pdf
2024-12-03 Update tmrIO
2024-12-03 tmrIO update
2024-12-03 adding fp-lib-table
2024-12-03 adding fp-info-cache
2024-12-03 Adding pdf
2024-12-04 Adding transistor
2024-12-04 Changing tekst preferences
2024-12-05 Adding DVI
2024-12-05 Routing DVI
2024-12-05 DVI update
2024-12-06 Adding initial MikroBus
2024-12-06 Routing extensions
2024-12-06 Adding MikroBus logo
2024-12-06 Cleanup MikroBus
2024-12-07 Adding initial eduIO board
2024-12-07 Adding PCA9535
2024-12-08 Adding initial adcIO
2024-12-08 Updating USB
2024-12-09 Adding ethIO
2024-12-09 Updating ethIO
2024-12-09 Adding README, updating picture
2024-12-09 README update
2024-12-10 Adding voltage level converter for USB
2024-12-10 Adding camIO
2024-12-10 Adding camIO pic
2024-12-10 fix #1
2024-12-10 Removing U1 as it is not needed - #4
2024-12-10 sch cleanup - reference cleanup
2024-12-10 Adding LP pins on P side of diff pair #4
2024-12-11 Adding termination #4
2024-12-11 .gitignore
2024-12-11 Adding production files
2024-12-11 Updating ethIO license
2024-12-13 Adding audio stp
2024-12-13 Updating picture
2025-04-01 Moving schematics to v9 adding more details
2025-04-07 Updating schematics moving to v9
2025-04-07 Update to KiCad v9
2025-04-07 Moving to v9
2025-04-09 napravljena promjena dolje desno
2025-04-24 Fix #7
2025-04-24 Fix #6
2025-04-24 Fix #5
2025-06-30 V0.2 dualTranslation - it should now work
